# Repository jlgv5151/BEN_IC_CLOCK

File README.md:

# BEN_IC_CLOCK
Following Ben Eater  IC Clock

Please follow the project in his website https://eater.net
He is providing a great kit for the project.

Modifications:

2026-08-29
- I'm adding some large 7 segment displays requiring 10v. Need to change and modify the PowerSupply
- Created a PCB to interface individually with each display.
- Note his project is using a Cathode 7 segment display. I will have to make some changes for future
- May using some different chips around the logic.

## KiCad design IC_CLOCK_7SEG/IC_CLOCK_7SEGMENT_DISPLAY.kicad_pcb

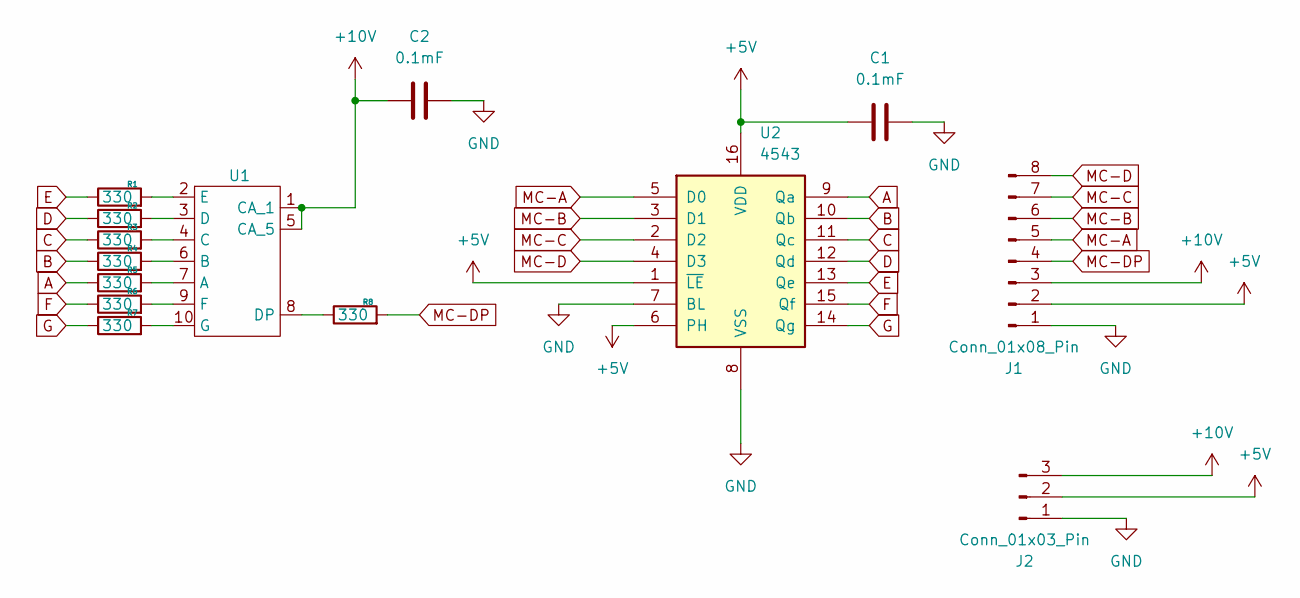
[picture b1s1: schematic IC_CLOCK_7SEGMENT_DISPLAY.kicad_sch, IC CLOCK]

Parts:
C1, C2: 0.1mF; C_1210_3225Metric_Pad1.33x2.70mm_HandSolder
J1: Conn_01x08_Pin; PinHeader_1x08_P2.54mm_Horizontal
J2: Conn_01x03_Pin; PinHeader_1x03_P2.54mm_Horizontal
R1, R2, R3, R4, R5, R6, R7, R8: 330; R_1206_3216Metric_Pad1.30x1.75mm_HandSolder
U1: DISP_CA_70mmX50mm
U2: 4543; DIP-16_W7.62mm

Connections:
+5V: C1.2, J1.2, J2.2, U2.1 (~LE), U2.6 (PH), U2.16 (VDD)
+10V: C2.2, J1.3, J2.3, U1.1 (CA_1), U1.5 (CA_5)
A: R5.1, U2.9 (Qa)
B: R4.1, U2.10 (Qb)
C: R3.1, U2.11 (Qc)
D: R2.1, U2.12 (Qd)
E: R1.1, U2.13 (Qe)
F: R6.1, U2.15 (Qf)
G: R7.1, U2.14 (Qg)
GND: C1.1, C2.1, J1.1, J2.1, U2.7 (BL), U2.8 (VSS)
MC-A: J1.5, U2.5 (D0)
MC-B: J1.6, U2.3 (D1)
MC-C: J1.7, U2.2 (D2)
MC-D: J1.8, U2.4 (D3)
MC-DP: J1.4, R8.2
unnamed: R5.2, U1.7 (A)
unnamed: R4.2, U1.6 (B)
unnamed: R3.2, U1.4 (C)
unnamed: R2.2, U1.3 (D)
unnamed: R8.1, U1.8 (DP)
unnamed: R1.2, U1.2 (E)
unnamed: R6.2, U1.9 (F)
unnamed: R7.2, U1.10 (G)

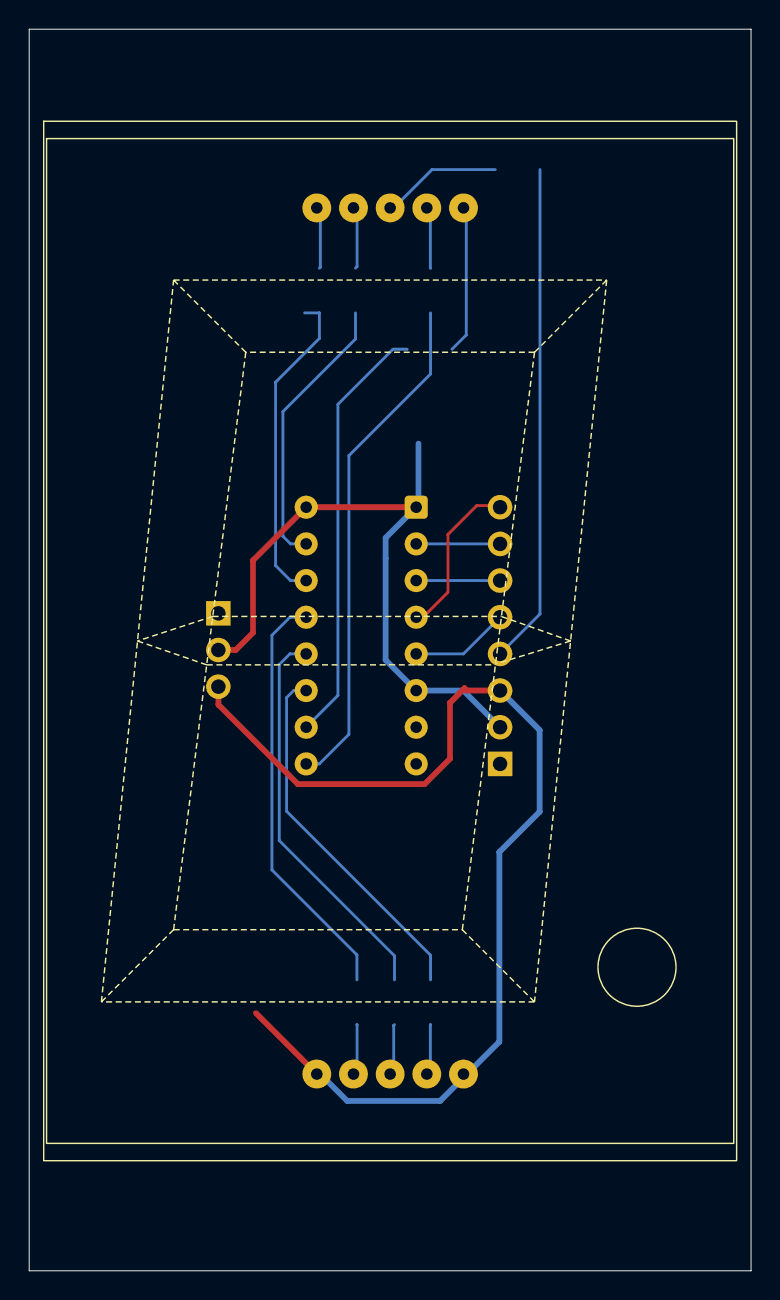
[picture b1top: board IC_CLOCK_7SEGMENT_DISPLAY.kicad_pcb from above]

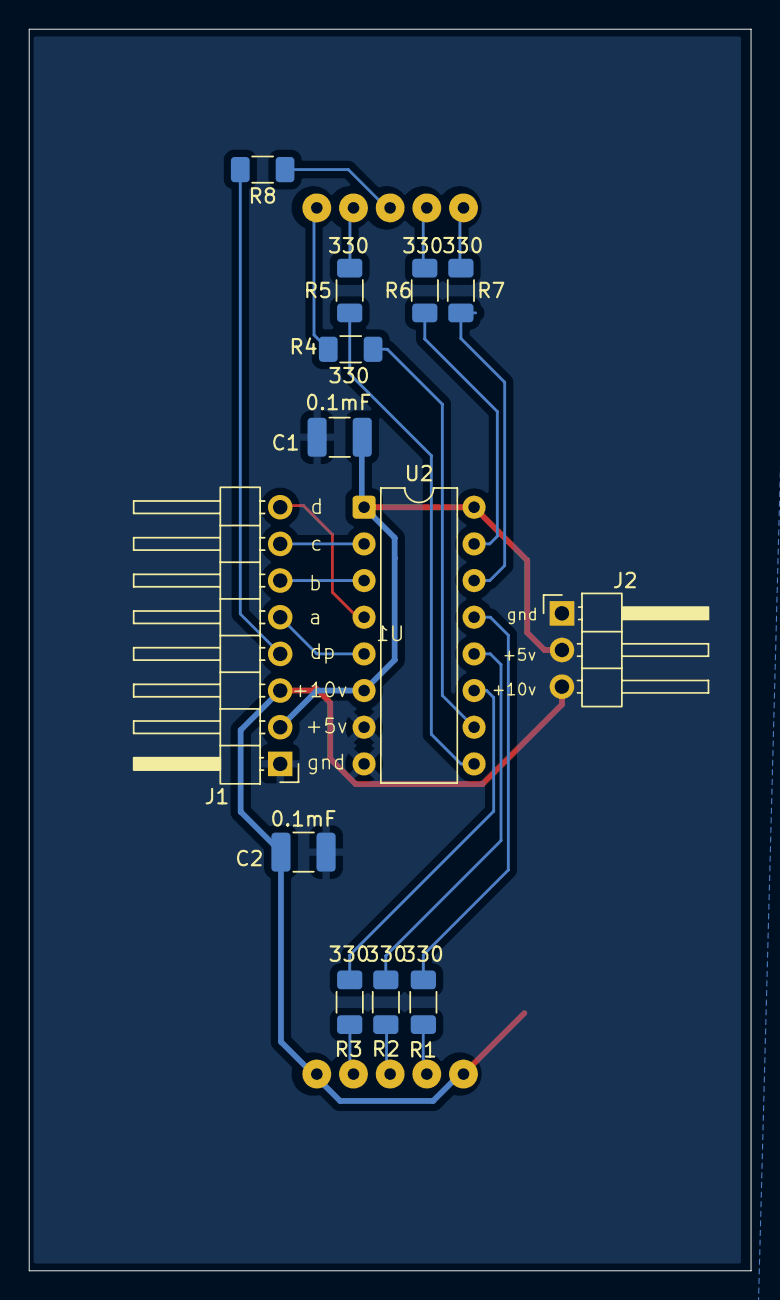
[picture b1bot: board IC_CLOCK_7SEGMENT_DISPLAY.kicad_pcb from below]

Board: 2 copper layers, 50.0 x 86.0 mm, 14 parts (13 on the bottom side), 23 nets.

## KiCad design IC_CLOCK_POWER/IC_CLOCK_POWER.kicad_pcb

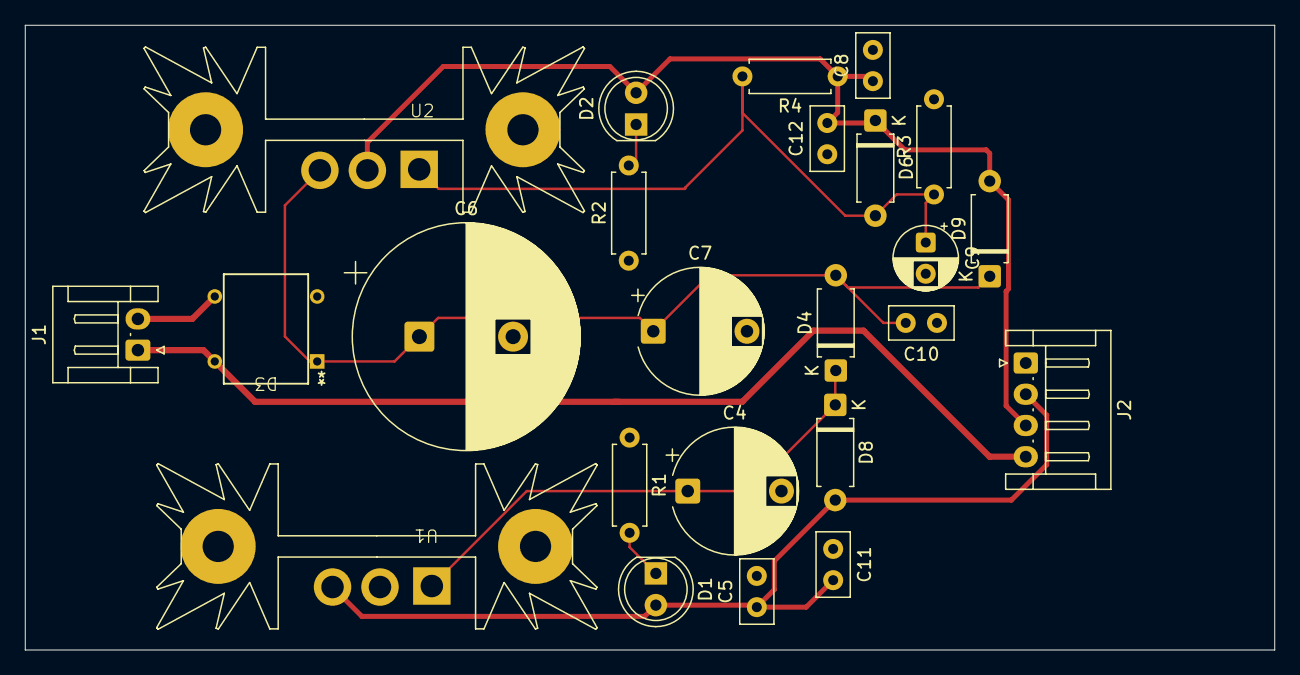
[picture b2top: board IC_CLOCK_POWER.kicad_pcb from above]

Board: 2 copper layers, 100.0 x 50.0 mm, 24 parts (0 on the bottom side), 10 nets.

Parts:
C4: 0.33u; CP_Radial_D10.0mm_P7.50mm
C5, C10, C11, C12: 0.1u; C_Disc_D5.0mm_W2.5mm_P2.50mm
C6: 10000u; CP_Radial_D18.0mm_P7.50mm
C7: 10mF; CP_Radial_D10.0mm_P7.50mm
C8: 1u; C_Disc_D5.0mm_W2.5mm_P2.50mm
C9: 10u; CP_Radial_D5.0mm_P2.50mm
D1: Green; LED_D5.0mm
D2: Yellow; LED_D5.0mm
D3: Bridge_Rectifiers; Bridge_Rectifier_4EDIP
D4, D6, D8, D9: 1N4002; D_A-405_P7.62mm_Horizontal
J1: Conn_01x02_Pin; JST_EH_S2B-EH_1x02_P2.50mm_Horizontal
J2: Conn_01x04_Pin; JST_EH_S4B-EH_1x04_P2.50mm_Horizontal
R1: r=330; R_Axial_DIN0207_L6.3mm_D2.5mm_P7.62mm_Horizontal
R2: 1k; R_Axial_DIN0207_L6.3mm_D2.5mm_P7.62mm_Horizontal
R3: 5K; R_Axial_DIN0207_L6.3mm_D2.5mm_P7.62mm_Horizontal
R4: 240; R_Axial_DIN0207_L6.3mm_D2.5mm_P7.62mm_Horizontal
U1: LM7805_TO220_HEAT_SINK; TO-220-HEADSINK-35X12
U2: LM317T; TO-220-HEADSINK-35X12

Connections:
12VAC: D3.4, J1.1, J2.4
+5V: C5.1, C11.2, D1.2 (A), D8.2 (A), J2.2, U1.3 (VO)
+10V: C8.1, C12.2, D2.2 (A), D6.1 (K), D9.2 (A), J2.3, R4.1, U2.2 (OUT)
AC-GND: D3.3, J1.2
GND: C4.2, C5.2, C6.2, C7.2, C8.2, C9.2, C10.1, C11.1, C12.1, D3.2 (-), J2.1, R1.1, R2.1, R3.2, U1.2 (GND)
unnamed: D1.1 (K), R1.2
unnamed: D2.1 (K), R2.2
unnamed: C6.1, C7.1, C10.2, D3.1 (+), D4.2 (A), D9.1 (K), U2.3 (IN)
unnamed: C4.1, D4.1 (K), D8.1 (K), U1.1 (VI)
unnamed: C9.1, D6.2 (A), R3.1, R4.2, U2.1 (ADJ)
